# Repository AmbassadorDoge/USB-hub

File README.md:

# USB HUB

- 2 USB-C 2.0 ports
- 2 USB-A 3.1 gen 1 ports
- Using TUSB8042, USB-A upstream
- ~80x54mm, all recepticles

- Need USB-A to ~ to connect with computer
- Only for data, please do not try to use for charging!

Made this because I needed a cheap and small USB hub I could carry so that my main hub could be kept at home. 

## Assembly

## PCB

|item   |price|link                                                                                                                                                                                                                                                                                                                                                                                                                                                                                                                                                          |
|-------|-----|--------------------------------------------------------------------------------------------------------------------------------------------------------------------------------------------------------------------------------------------------------------------------------------------------------------------------------------------------------------------------------------------------------------------------------------------------------------------------------------------------------------------------------------------------------------|
|PCB    | $7  | jlcpcb.com                                                                                                                                                                                                                                                                                                                                                                                                                                                                                                                                                   |
|PCBA   | $45 | jlcpcb.com                                                                                                                                                                                                                                                                                                                                                                                                                                                                                                                                                   |
|acrylic| $5  | https://www.amazon.com/FixtureDisplays%C2%AE-Nominal-Plexiglass-Tabletop-15643-6X6-NF/dp/B099Z3Y54B/ref=sr_1_1?crid=12MRUGLYQPM08&dib=eyJ2IjoiMSJ9.bwrXUXJPVfEUUGOcstb6OW1oUdJJFdomVWIMQsuaZkJ3_09hpqhV_a-v3yTYfOb5qmMfEHIglMSmT0vqpHroCT4pgpX9o3cJ-CnE6EuJb21ijxaJErLLQqhbtIVr0c5sW9LJajPZzOmUxOwJVahXBGl0Mx85-z_kaoHjkkQNpACKRNvT19Wp-fUhGlJ76hLlMfA6y4T6kVjPZdRpd1XvQYlomg0bObWw_zlLg006bQM.llWVyWuKthsq_PDd4JOVll7m-l5nJDtawurICGI3NF8&dib_tag=se&keywords=acrylic%2Bsheet%2B1%2F8&qid=1773094932&sprefix=acrylic%2Bsheet%2B1%2F8%2Caps%2C185&sr=8-1&th=1|
|total  | $52 | -                                                                                                                                                                                                                                                                                                                                                                                                                                                                                                                                                            |

Made using KiCad & Onshape
[Onshape link](https://cad.onshape.com/documents/166e42de1b24c1a1952d9a0a/w/ee2553dc721c4a7be2e464a8/e/28846ffd7bfde794f9e65d97)

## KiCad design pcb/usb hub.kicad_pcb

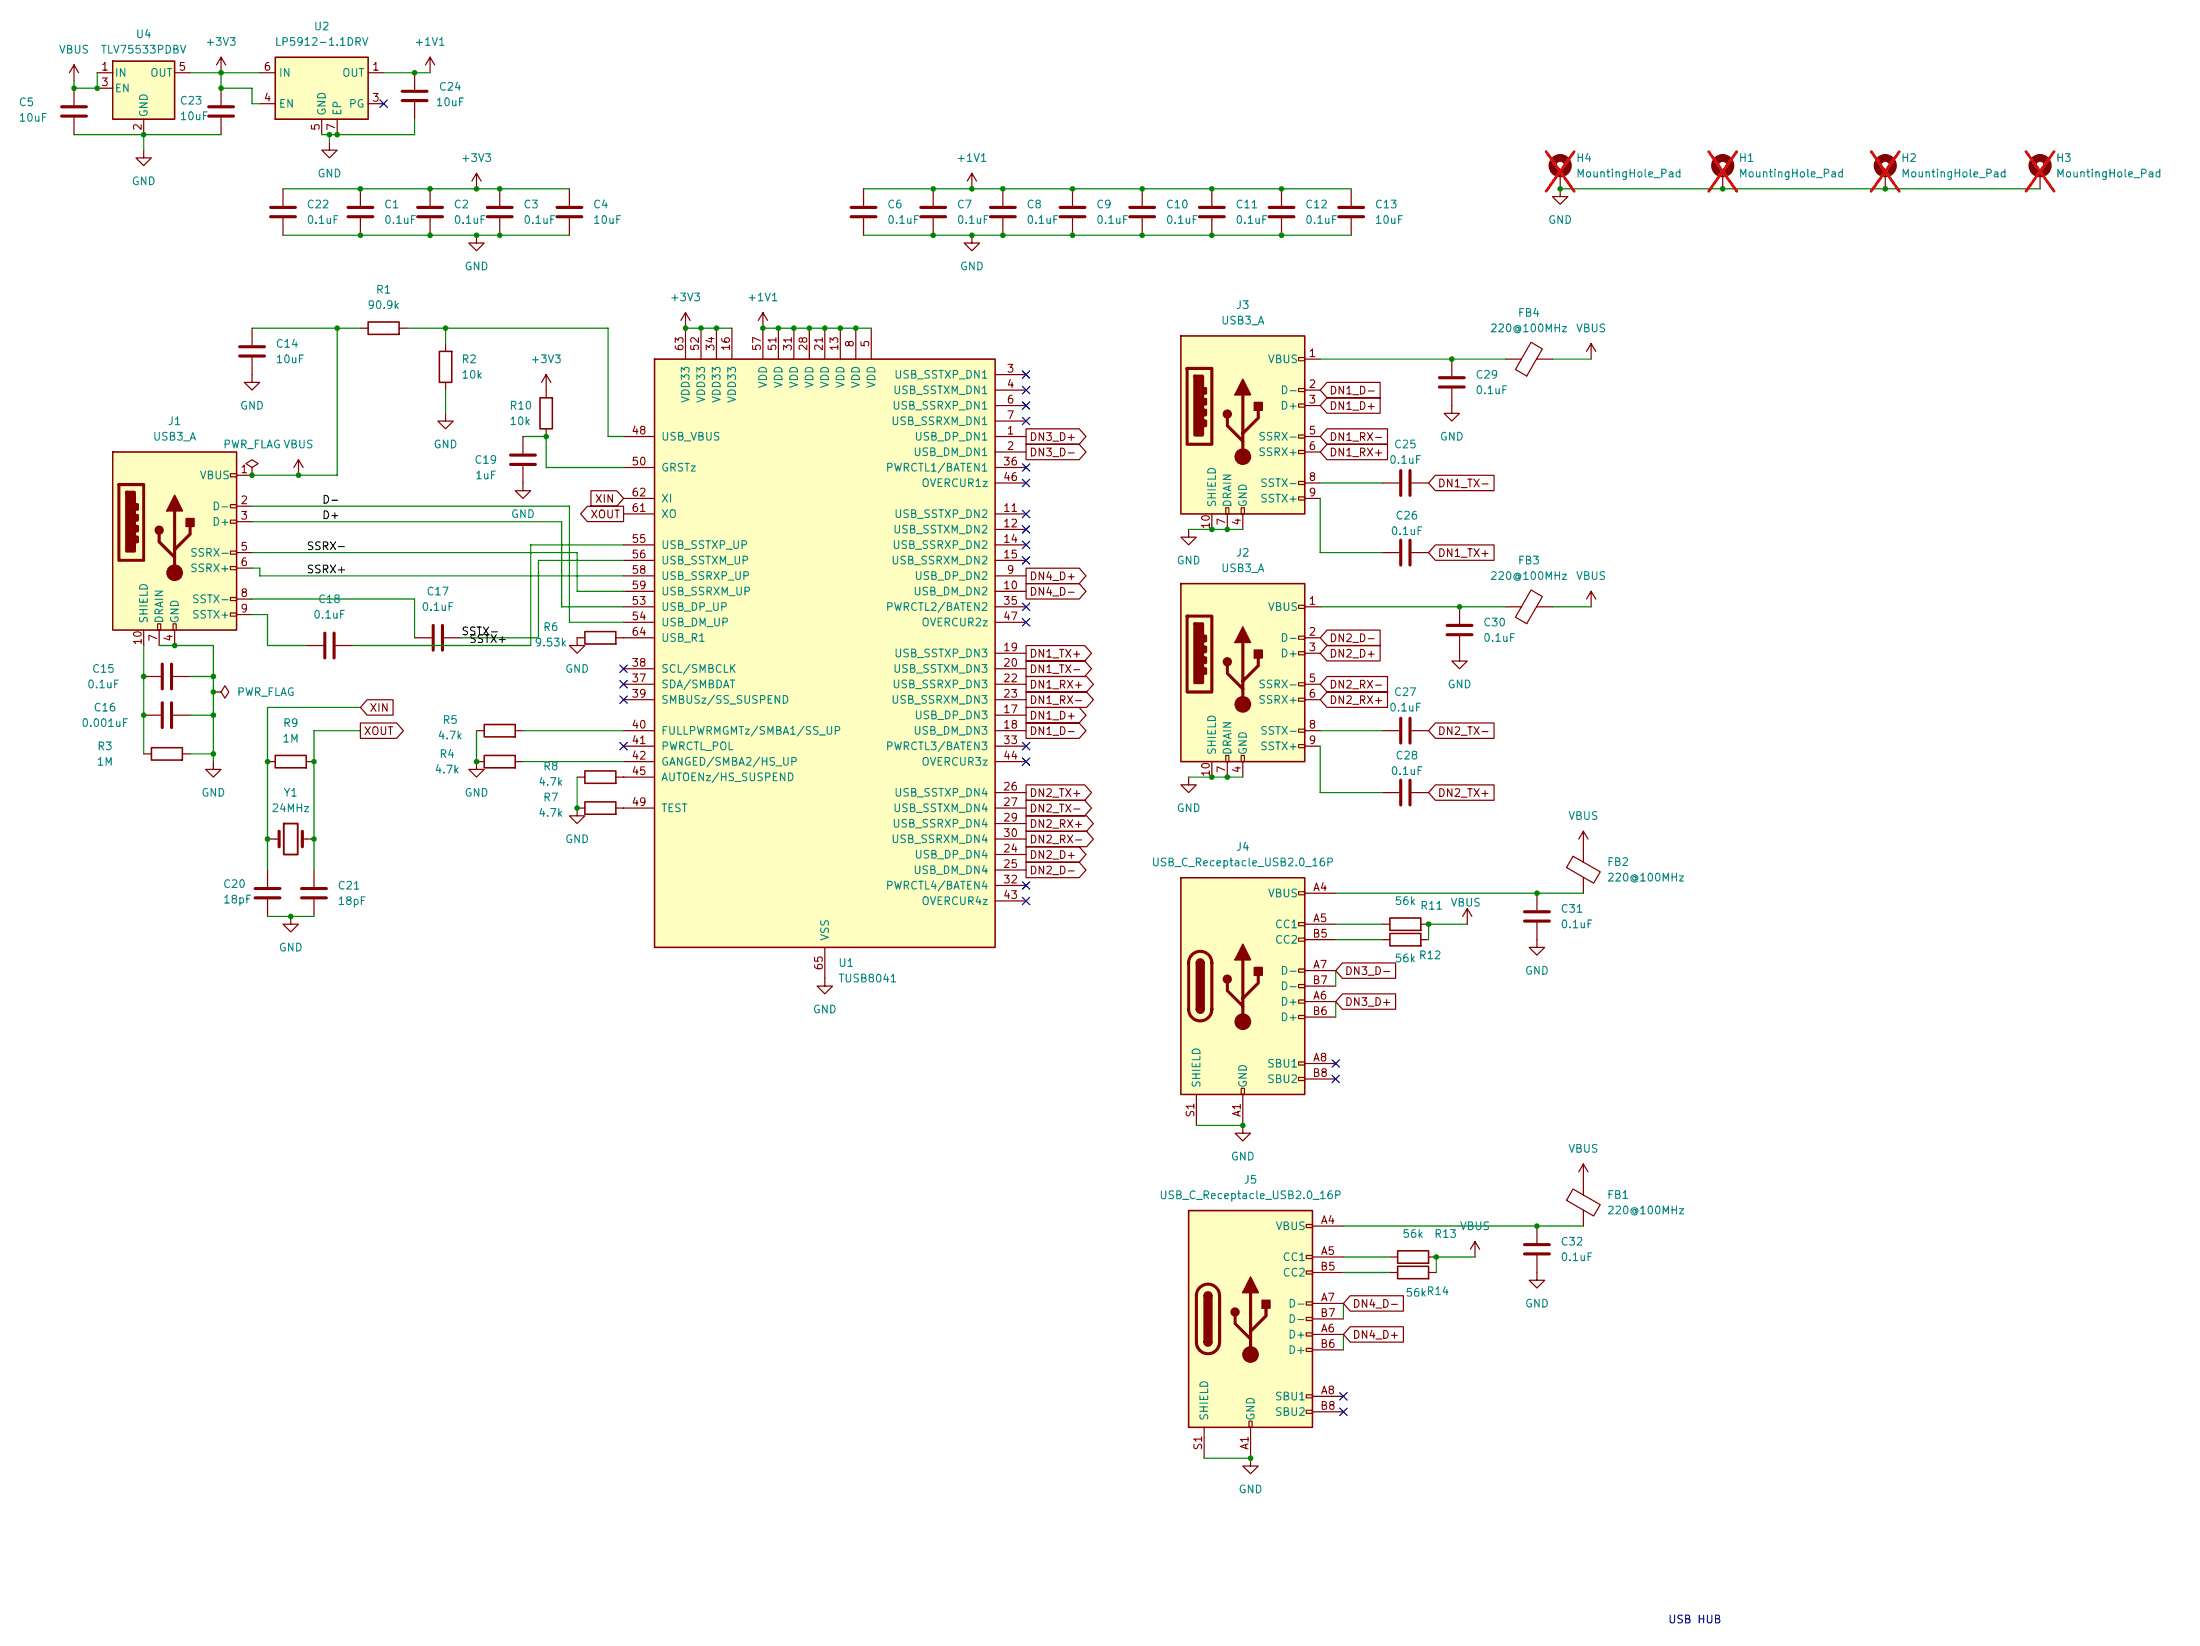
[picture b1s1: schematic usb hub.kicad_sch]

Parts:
C1, C2, C3, C6, C7, C8, C9, C10, C11, C12, C15, C17, C18, C22, C25, C26, C27, C28, C29, C30, C31, C32: 0.1uF; C_0402_1005Metric
C4, C5, C13, C14, C23, C24: 10uF; C_0805_2012Metric
C16: 0.001uF; C_0402_1005Metric
C19: 1uF; C_0402_1005Metric
C20, C21: 18pF; C_0402_1005Metric
FB1, FB2, FB3, FB4: 220@100MHz; L_0402_1005Metric
H1, H2, H3, H4: MountingHole_Pad; MountingHole_3.2mm_M3_Pad; not fitted
J1, J2, J3: USB3_A; USB3_A_Receptacle_Wuerth_692122030100
J4, J5: USB_C_Receptacle_USB2.0_16P; USB_C_Receptacle_GCT_USB4105-xx-A_16P_TopMnt_Horizontal
R1: 90.9k; R_0402_1005Metric
R2, R10: 10k; R_0402_1005Metric
R3, R9: 1M; R_0402_1005Metric
R4, R5, R7, R8: 4.7k; R_0402_1005Metric
R6: 9.53k; R_0402_1005Metric
R11, R12, R13, R14: 56k; R_0402_1005Metric
U1: TUSB8041; QFN-64-1EP_9x9mm_P0.5mm_EP6x6mm_ThermalVias
U2: LP5912-1.1DRV; WSON-6-1EP_2x2mm_P0.65mm_EP1x1.6mm_ThermalVias
U4: TLV75533PDBV; SOT-23-5
Y1: 24MHz; Crystal_SMD_3225-4Pin_3.2x2.5mm

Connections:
+1V1: C6.1, C7.1, C8.1, C9.1, C10.1, C11.1, C12.1, C13.1, C24.2, U1.5 (VDD), U1.8 (VDD), U1.13 (VDD), U1.21 (VDD), U1.28 (VDD), U1.31 (VDD), U1.51 (VDD), U1.57 (VDD), U2.1 (OUT)
+3V3: C1.1, C2.1, C3.1, C4.1, C22.1, C23.1, R10.2, U1.16 (VDD33), U1.34 (VDD33), U1.52 (VDD33), U1.63 (VDD33), U2.4 (EN), U2.6 (IN), U4.5 (OUT)
/D+: J1.3 (D+), U1.53 (USB_DP_UP)
/D-: J1.2 (D-), U1.54 (USB_DM_UP)
/SSRX+: J1.6 (SSRX+), U1.58 (USB_SSRXP_UP)
/SSRX-: J1.5 (SSRX-), U1.59 (USB_SSRXM_UP)
/SSTX+: C18.2, U1.55 (USB_SSTXP_UP)
/SSTX-: C17.2, U1.56 (USB_SSTXM_UP)
DN1_D+: J3.3 (D+), U1.17 (USB_DP_DN3)
DN1_D-: J3.2 (D-), U1.18 (USB_DM_DN3)
DN1_RX+: J3.6 (SSRX+), U1.22 (USB_SSRXP_DN3)
DN1_RX-: J3.5 (SSRX-), U1.23 (USB_SSRXM_DN3)
DN1_TX+: C26.2, U1.19 (USB_SSTXP_DN3)
DN1_TX-: C25.2, U1.20 (USB_SSTXM_DN3)
DN2_D+: J2.3 (D+), U1.24 (USB_DP_DN4)
DN2_D-: J2.2 (D-), U1.25 (USB_DM_DN4)
DN2_RX+: J2.6 (SSRX+), U1.29 (USB_SSRXP_DN4)
DN2_RX-: J2.5 (SSRX-), U1.30 (USB_SSRXM_DN4)
DN2_TX+: C28.2, U1.26 (USB_SSTXP_DN4)
DN2_TX-: C27.2, U1.27 (USB_SSTXM_DN4)
DN3_D+: J4.A6 (D+), J4.B6 (D+), U1.1 (USB_DP_DN1)
DN3_D-: J4.A7 (D-), J4.B7 (D-), U1.2 (USB_DM_DN1)
DN4_D+: J5.A6 (D+), J5.B6 (D+), U1.9 (USB_DP_DN2)
DN4_D-: J5.A7 (D-), J5.B7 (D-), U1.10 (USB_DM_DN2)
GND: C1.2, C2.2, C3.2, C4.2, C5.2, C6.2, C7.2, C8.2, C9.2, C10.2, C11.2, C12.2, C13.2, C14.2, C15.2, C16.2, C19.1, C20.2, C21.2, C22.2, C23.2, C24.1, C29.1, C30.1, C31.1, C32.1, H1.1, H2.1, H3.1, H4.1, J1.4 (GND), J1.7 (DRAIN), J2.4 (GND), J2.7 (DRAIN), J2.10 (SHIELD), J3.4 (GND), J3.7 (DRAIN), J3.10 (SHIELD), J4.A1 (GND), J4.A12 (GND), J4.B1 (GND), J4.B12 (GND), J4.S1 (SHIELD), J5.A1 (GND), J5.A12 (GND), J5.B1 (GND), J5.B12 (GND), J5.S1 (SHIELD), R2.1, R3.2, R4.1, R5.1, R6.1, R7.1, R8.1, U1.65 (VSS), U2.5 (GND), U2.7 (EP), U4.2 (GND)
unnamed: C31.2, FB2.2, J4.A4 (VBUS), J4.A9 (VBUS), J4.B4 (VBUS), J4.B9 (VBUS)
unnamed: C32.2, FB1.2, J5.A4 (VBUS), J5.A9 (VBUS), J5.B4 (VBUS), J5.B9 (VBUS)
unnamed: C15.1, C16.1, J1.10 (SHIELD), R3.1
unnamed: C18.1, J1.9 (SSTX+)
unnamed: C17.1, J1.8 (SSTX-)
unnamed: C28.1, J2.9 (SSTX+)
unnamed: C27.1, J2.8 (SSTX-)
unnamed: C30.2, FB3.1, J2.1 (VBUS)
unnamed: C26.1, J3.9 (SSTX+)
unnamed: C25.1, J3.8 (SSTX-)
unnamed: C29.2, FB4.1, J3.1 (VBUS)
unnamed: J4.A5 (CC1), R11.1
unnamed: J4.B5 (CC2), R12.1
unnamed: J5.A5 (CC1), R13.1
unnamed: J5.B5 (CC2), R14.1
unnamed: R8.2, U1.45 (AUTOENz/HS_SUSPEND)
unnamed: R5.2, U1.40 (FULLPWRMGMTz/SMBA1/SS_UP)
unnamed: R4.2, U1.42 (GANGED/SMBA2/HS_UP)
unnamed: C19.2, R10.1, U1.50 (GRSTz)
unnamed: R7.2, U1.49 (TEST)
unnamed: R6.2, U1.64 (USB_R1)
unnamed: R1.2, R2.2, U1.48 (USB_VBUS)
VBUS: C5.1, C14.1, FB1.1, FB2.1, FB3.2, FB4.2, J1.1 (VBUS), R1.1, R11.2, R12.2, R13.2, R14.2, U4.1 (IN), U4.3 (EN)
XIN: C20.1, R9.1, U1.62 (XI), Y1.1
XOUT: C21.1, R9.2, U1.61 (XO), Y1.2

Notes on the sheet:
USB HUB

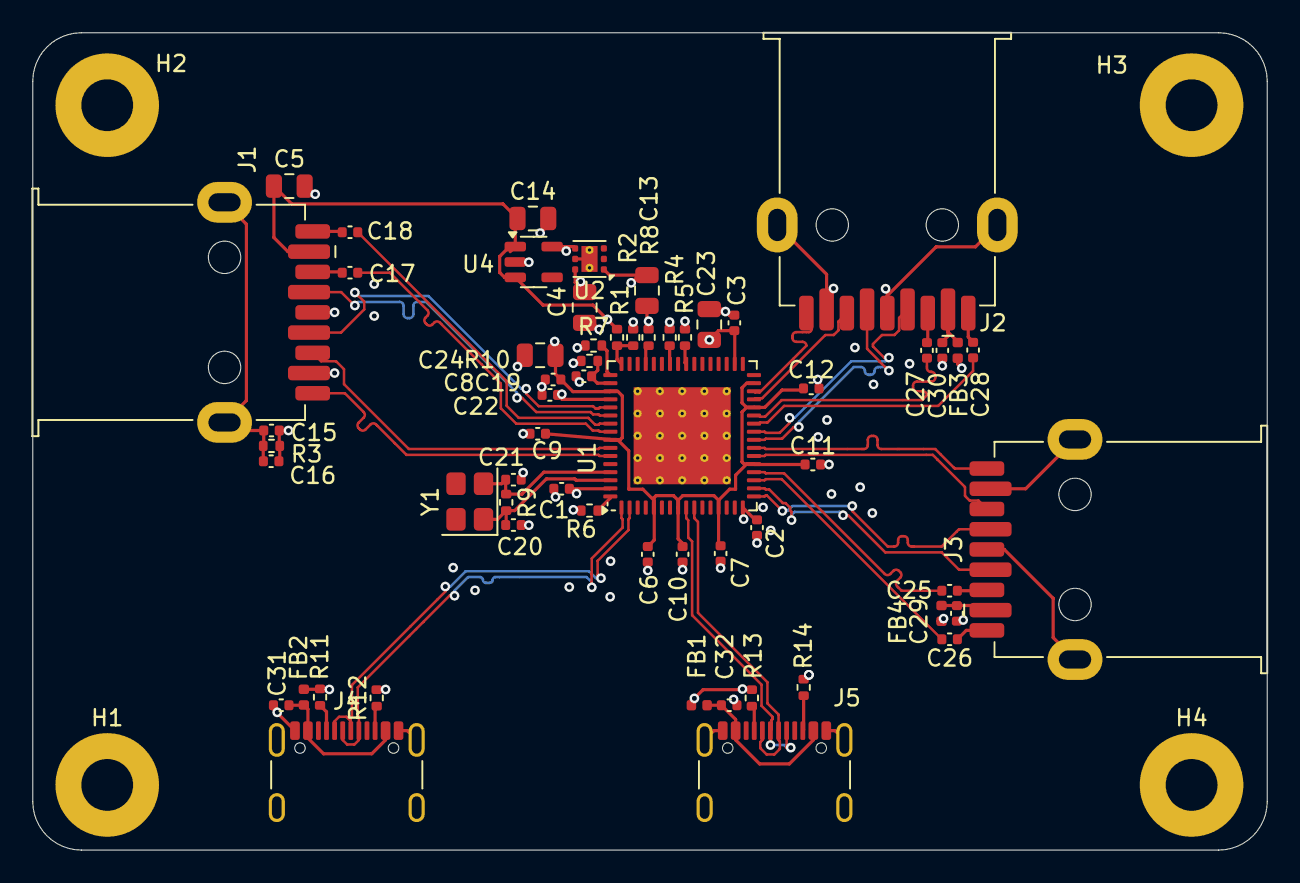
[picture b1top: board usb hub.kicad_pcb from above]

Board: 4 copper layers, 76.3 x 50.5 mm, 63 parts (0 on the bottom side), 50 nets.

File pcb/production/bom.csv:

Designator,Footprint,Quantity,Value,LCSC Part #
"C1, C10, C11, C12, C15, C17, C18, C2, C22, C25, C26, C27, C28, C29, C3, C30, C31, C32, C6, C7, C8, C9",0402,22,0.1uF,
"C13, C14, C23, C24, C4, C5",0805,6,10uF,
C16,0402,1,0.001uF,
C19,0402,1,1uF,
"C20, C21",0402,2,18pF,
"FB1, FB2, FB3, FB4",0402,4,220@100MHz,
"J1, J2, J3",USB3_A_Receptacle_Wuerth_692122030100,3,USB3_A,
"J4, J5",USB_C_Receptacle_GCT_USB4105-xx-A_16P_TopMnt_Horizontal,2,USB_C_Receptacle_USB2.0_16P,
R1,0402,1,90.9k,
"R10, R2",0402,2,10k,
"R11, R12, R13, R14",0402,4,56k,
"R3, R9",0402,2,1M,
"R4, R5, R7, R8",0402,4,4.7k,
R6,0402,1,9.53k,
U1,QFN-64-1EP_9x9mm_P0.5mm_EP6x6mm_ThermalVias,1,TUSB8041,
U2,WSON-6-1EP_2x2mm_P0.65mm_EP1x1.6mm_ThermalVias,1,LP5912-1.1DRV,
U4,SOT-23-5,1,TLV75533PDBV,
Y1,Crystal_SMD_3225-4Pin_3.2x2.5mm,1,24MHz,

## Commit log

2026-03-09 Add pictures
2026-03-09 add acrylic + link
2026-03-13 Modify Onshape link in README
    Updated Onshape link to include render mode and UI state parameters.
